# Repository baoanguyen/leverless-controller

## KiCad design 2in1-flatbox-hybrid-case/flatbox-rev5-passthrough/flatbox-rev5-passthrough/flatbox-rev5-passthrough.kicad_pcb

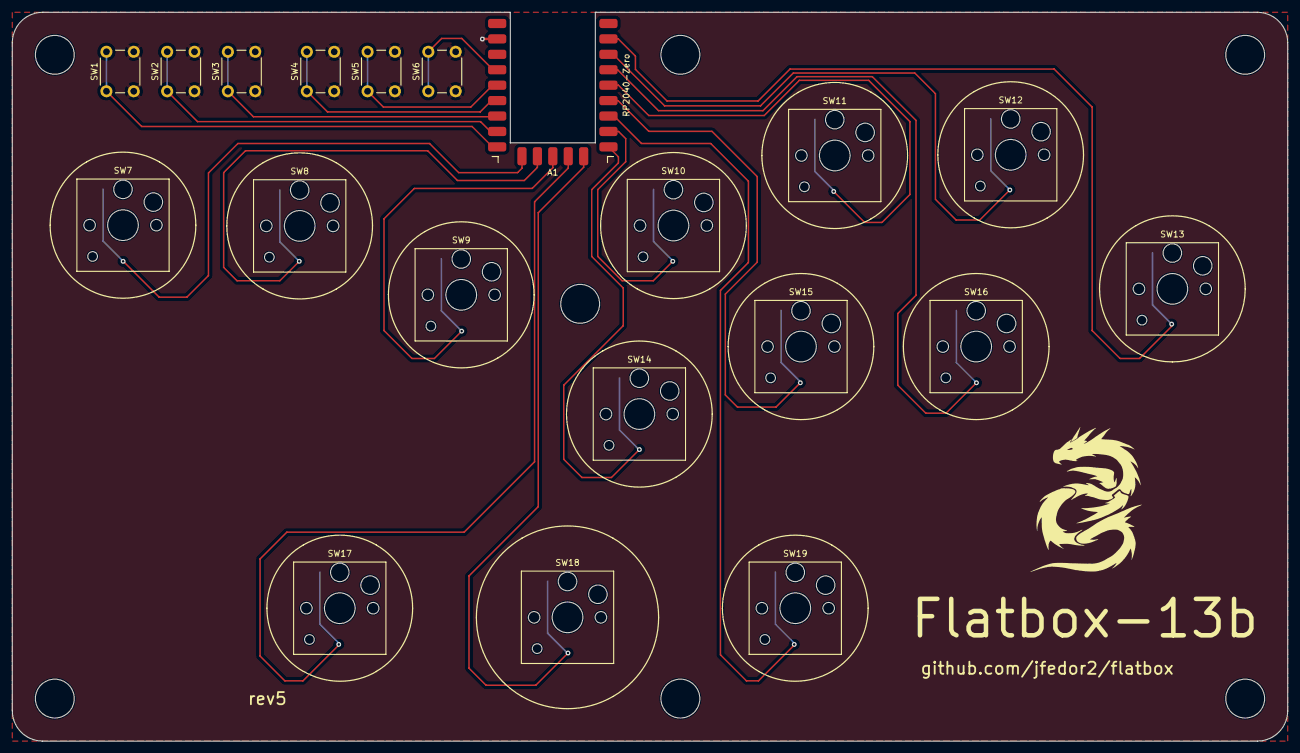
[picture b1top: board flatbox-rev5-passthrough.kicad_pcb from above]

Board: 2 copper layers, 210.0 x 120.0 mm, 28 parts (0 on the bottom side), 19 nets.

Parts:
A1: RP2040-Zero
H1, H2, H3, H4, H5, H6, H7: MountingHole; MountingHole_6.4mm_M6
SW1, SW2, SW3, SW4, SW5, SW6: SW_Push; SW_PUSH_6mm_H5mm
SW7, SW8, SW9, SW10, SW11, SW12, SW13, SW14, SW15, SW16, SW17, SW18, SW19: SW_Push; SW_Hotswap_Kailh_Choc_V1V2
leviathan-logo: LOGO

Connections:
CIRCLE: A1.6 (GPIO5), SW15.1
CROSS: A1.9 (GPIO8), SW14.1
DOWN: A1.13 (GPIO12), SW8.1
GND: A1.23 (GND), SW1.2, SW2.2, SW3.2, SW4.2, SW5.2, SW6.2, SW7.2, SW8.2, SW9.2, SW10.2, SW11.2, SW12.2, SW13.2, SW14.2, SW15.2, SW16.2, SW17.2, SW18.2, SW19.2
L1: A1.7 (GPIO6), SW19.1
L2: A1.11 (GPIO10), SW17.1
LEFT: A1.14 (GPIO13), SW7.1
OPT1: A1.15 (GPIO14), SW1.1
OPT2: A1.16 (GPIO15), SW2.1
OPT3: A1.17 (GPIO26), SW3.1
OPT4: A1.18 (GPIO27), SW4.1
OPT5: A1.19 (GPIO28), SW5.1
OPT6: A1.20 (GPIO29), SW6.1
R1: A1.3 (GPIO2), SW12.1
R2: A1.4 (GPIO3), SW16.1
RIGHT: A1.12 (GPIO11), SW9.1
SQUARE: A1.8 (GPIO7), SW10.1
TRIANGLE: A1.5 (GPIO4), SW11.1
UP: A1.10 (GPIO9), SW18.1

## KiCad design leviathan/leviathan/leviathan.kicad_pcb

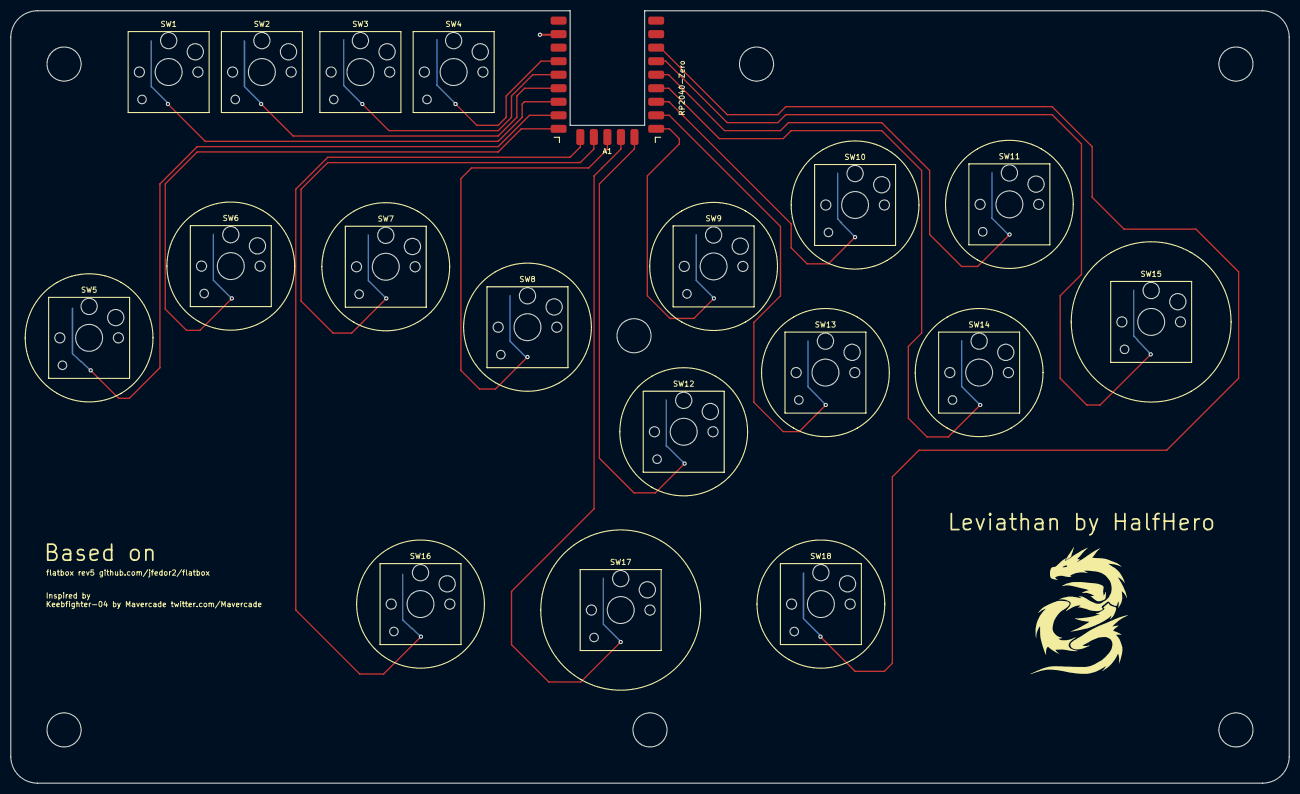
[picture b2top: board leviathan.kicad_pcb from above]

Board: 2 copper layers, 240.0 x 145.0 mm, 27 parts (0 on the bottom side), 19 nets.

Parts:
A1: RP2040-Zero
H1, H2, H3, H4, H5, H6, H7: MountingHole; MountingHole_6.4mm_M6
SW1, SW2, SW3, SW4: SW_Push; SW_Hotswap_Kailh_Choc_V1V2_1.00u
SW5, SW6, SW7, SW8, SW9, SW10, SW11, SW12, SW13, SW14, SW15, SW16, SW17, SW18: SW_Push; SW_Hotswap_Kailh_Choc_V1V2
leviathan-logo: LOGO

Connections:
CIRCLE: A1.8 (GPIO7), SW13.1
CROSS: A1.10 (GPIO9), SW12.1
DOWN: A1.13 (GPIO12), SW7.1
GND: A1.23 (GND), SW1.2, SW2.2, SW3.2, SW4.2, SW5.2, SW6.2, SW7.2, SW8.2, SW9.2, SW10.2, SW11.2, SW12.2, SW13.2, SW14.2, SW15.2, SW16.2, SW17.2, SW18.2
L1: A1.4 (GPIO3), SW15.1
L2: A1.3 (GPIO2), SW18.1
LEFT: A1.15 (GPIO14), SW6.1
OPT1: A1.17 (GPIO26), SW1.1
OPT2: A1.18 (GPIO27), SW2.1
OPT3: A1.16 (GPIO15), SW5.1
OPT4: A1.14 (GPIO13), SW16.1
OPT5: A1.19 (GPIO28), SW3.1
OPT6: A1.20 (GPIO29), SW4.1
R1: A1.5 (GPIO4), SW11.1
R2: A1.6 (GPIO5), SW14.1
RIGHT: A1.12 (GPIO11), SW8.1
SQUARE: A1.9 (GPIO8), SW9.1
TRIANGLE: A1.7 (GPIO6), SW10.1
UP: A1.11 (GPIO10), SW17.1

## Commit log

2024-04-22 First iteration of PCB
2024-04-22 Added ground fill and fixed PCB issues from schematic update
2024-04-24 Adding all the manufacturing files and CAD
2024-04-28 Added a hybrid case, based on flatbox-rev5. Is capable of CNC JLCPCB case but also acrylic tops
